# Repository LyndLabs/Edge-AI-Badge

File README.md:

# Edge AI Foundation Badge

The Edge AI Badge lets you plug-and-play with the latest vendor hardware at conference workshops and wirelessly connect with other attendees! Use the badge to explore the Edge AI curriculum, plug into sensors, and start building apps.

- 📄 [Read the docs →](https://lyndlabs.github.io/edge-ai-badge-docs)
- 💻 [Download or contribute to firmware](https://github.com/lyndlabs/edge-ai-badge-firmware).

## Hardware 
The badge is a modular PCB that allows you to customize your own face & backplates - the hardware platform is consistent at future conferences and makes it easy for attendees to design their own add-ons, or vendors that want to contribute hardware. 

It's built around the ESP32-S3, selected for its cryptographic core + secure boot, communication protocols (WiFi, BLE, ESP-NOW), infrared hardware, native USB, and ubiquitous support.

---

## Contents
- **assets**: logos, renders, global design assets
    - *find local assets under subfolders*
- **pcb**: KiCAD design files for `main`, `face`, `back`
- **fab**: production-ready pcb + laser files

## Versions & Notes
Versions bumped per batch release, revisions tracked for minor design changes per board - `main`, `face`, `back` tracked separately.

### v1 
- [x] Fixed USB + Power Path + XTAL issue 
- [ ] Buttons on resistor ladder
- [ ] Power button to MCU
- [ ] Standoff drill
- [ ] Interrupt to expansion
- [ ] Diode on USB 

### v0 - 26/06/08
- Main boards + backplate only - released in green HASL
- Wrong SMD standoff drilling size + CPL in production batch - used regular standoffs
- CPL + BOM discrepancy, released for visibility but pls do not order
- Known issue with USB charging
- Known issue w. Deep Sleep (.1uF caps on xtal)

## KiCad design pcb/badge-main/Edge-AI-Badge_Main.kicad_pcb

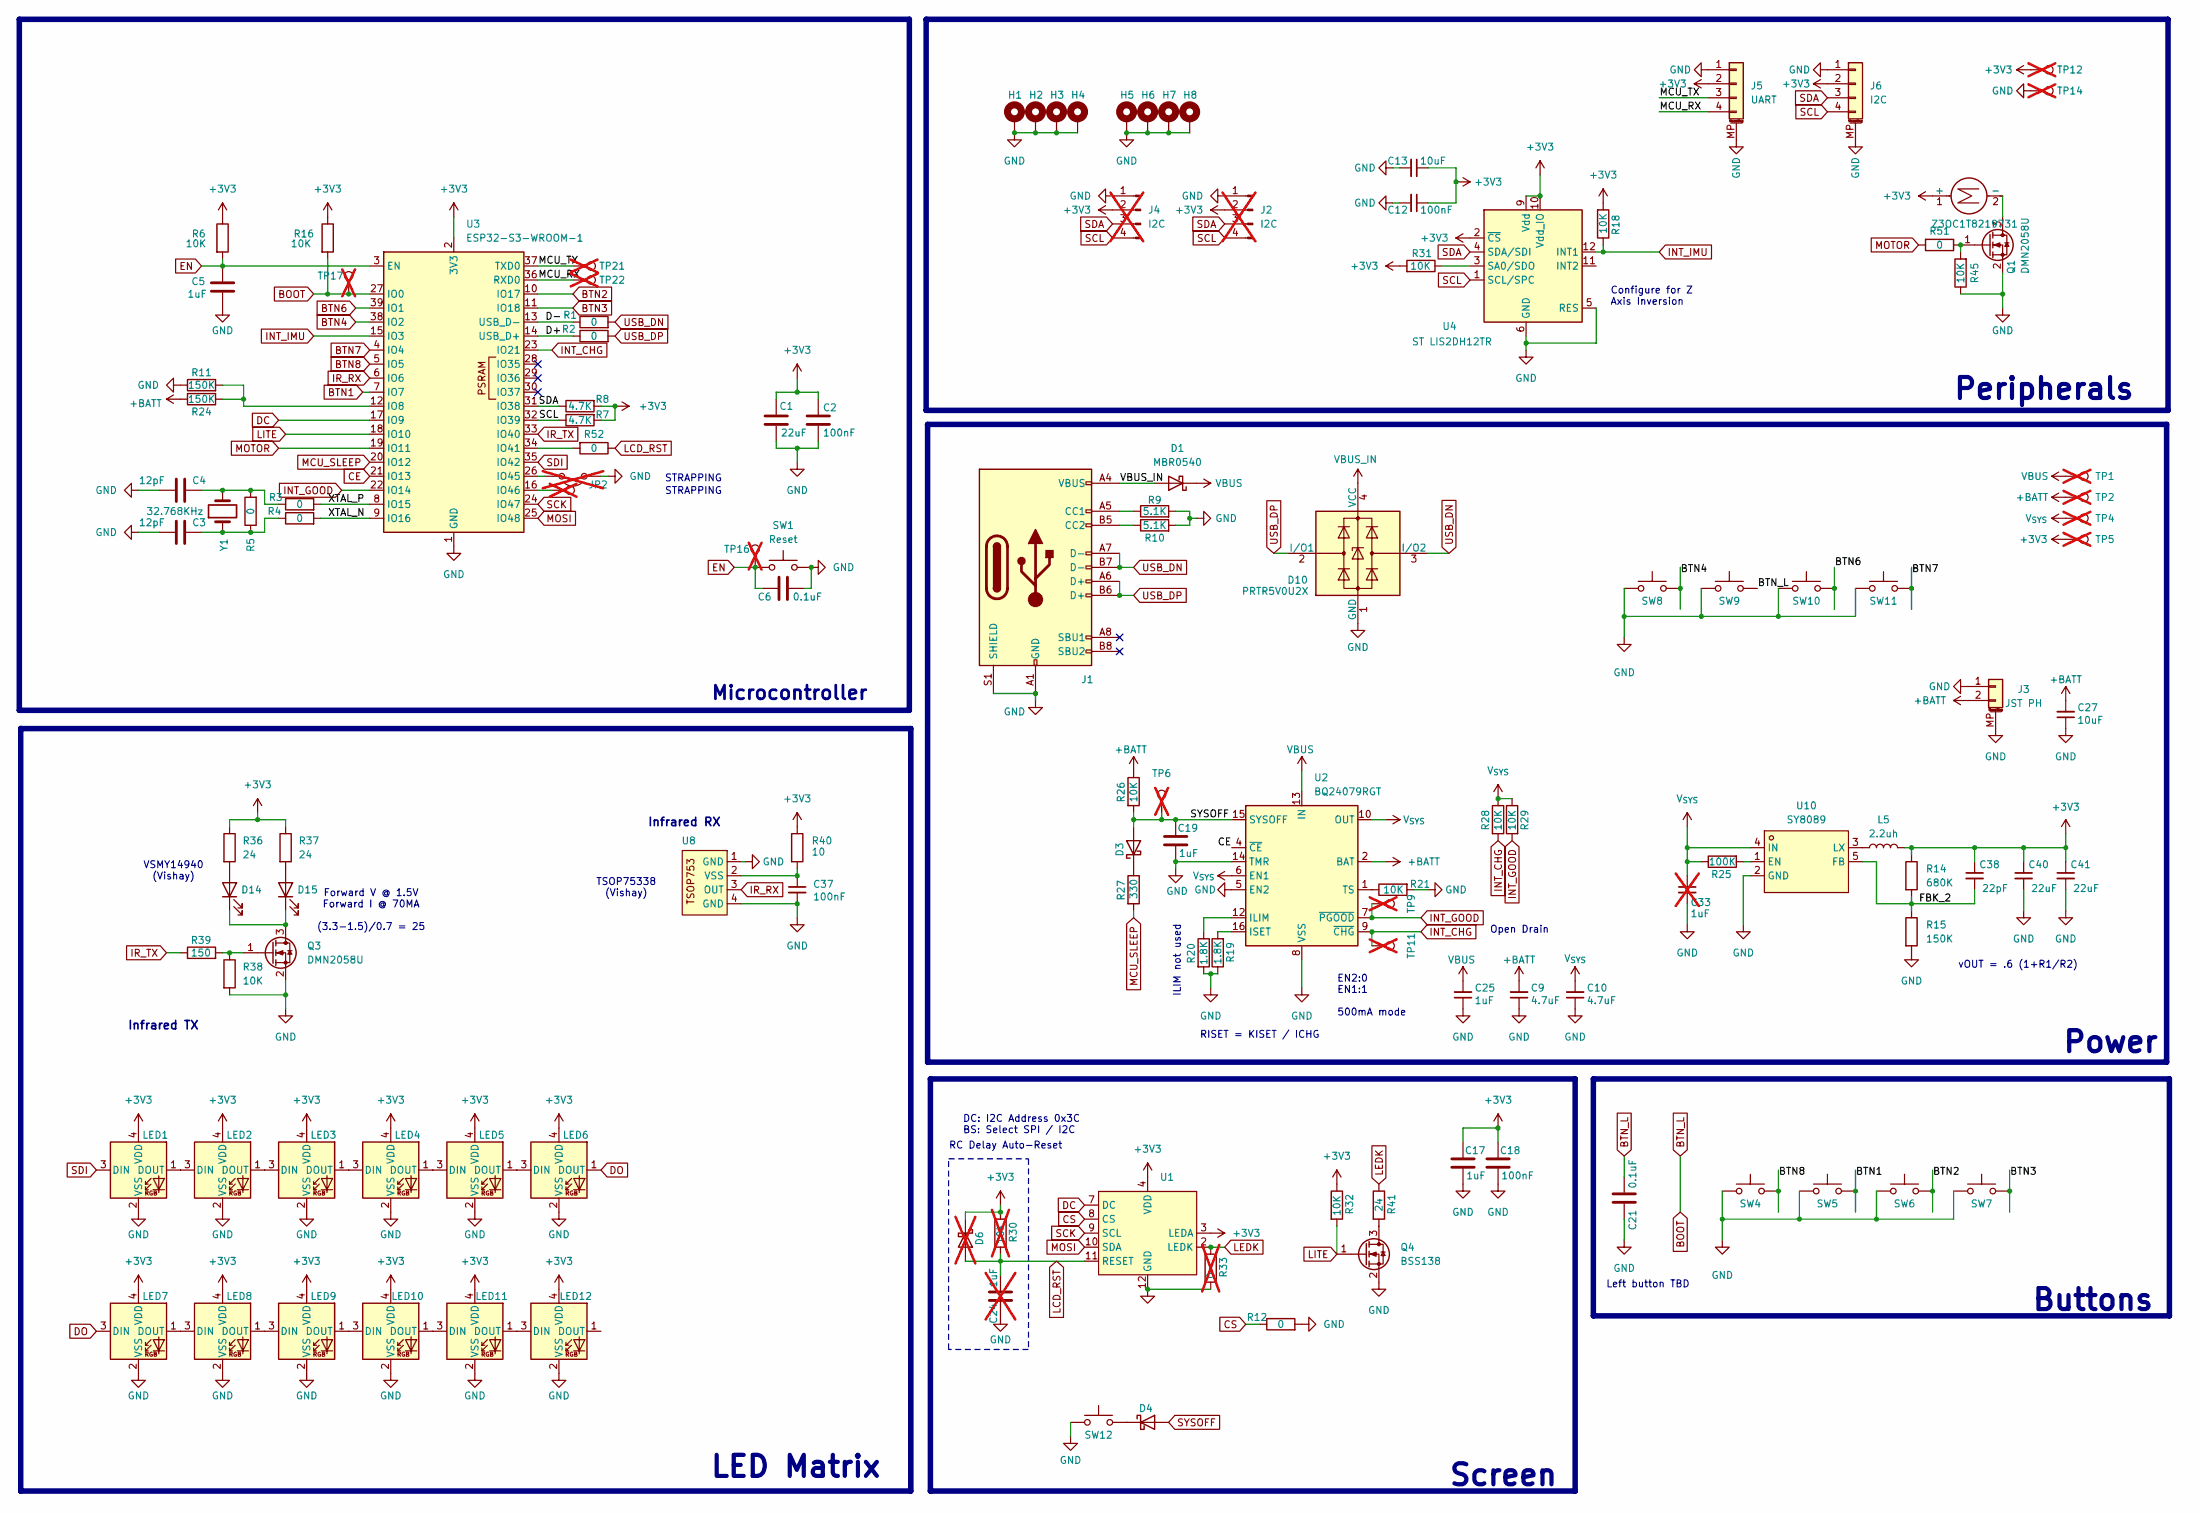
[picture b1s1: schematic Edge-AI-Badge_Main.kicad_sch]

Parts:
C1, C40, C41: 22uF; C_0402_1005Metric; LCSC C3845593
C2, C12, C18, C37: 100nF; C_0402_1005Metric; LCSC C1525
C3, C4: 12pF; C_0402_1005Metric; LCSC C1525
C5, C17, C19, C25: 1uF; C_0402_1005Metric; LCSC C14445
C6, C21: 0.1uF; C_0402_1005Metric; LCSC C1525
C9, C10: 4.7uF; C_0402_1005Metric; LCSC C315248
C13, C27: 10uF; C_0402_1005Metric; LCSC C315248
C24: 1uF; C_0402_1005Metric; LCSC C14445; not fitted
C33: 1uF; C_0402_1005Metric; LCSC C3845593; not fitted
C38: 22pF; C_0402_1005Metric; LCSC C76960
D1: MBR0540; D_SOD-123
D3, D4: D_Schottky; D_SOD-523; LCSC C917006
D6: D_Schottky; D_SOD-523; LCSC C917006; not fitted
D10: PRTR5V0U2X; SOT-143; LCSC C5180302
D14, D15: VSMY14940; vsmy14940; LCSC C511069
H1, H2, H3, H4, H5, H6, H7, H8: MountingHole_Pad
J1: USB C 2.0; USB_C_Receptacle_Palconn_UTC16-G; LCSC C2765186
J2, J4: I2C; PinSocket_1x04_P2.54mm_Vertical; not fitted
J3: JST PH; JST_PH_S2B-PH-SM4-TB_1x02-1MP_P2.00mm_Horizontal; LCSC C295747
J5: UART
J6: I2C
JP2: Jumper_2_Open; SolderJumper-2_P1.3mm_Open_RoundedPad1.0x1.5mm; not fitted
L5: 2.2uh; L_Coilcraft_LPS3010; LCSC C2926400
LED1, LED2, LED3, LED4, LED5, LED6, LED7, LED8, LED9, LED10, LED11, LED12: WS2812B-2020; LED_WS2812B-2020_PLCC4_2.0x2.0mm
M1: Z3OC1T8219731
Q1, Q3: DMN2058U; SOT-23; LCSC C461001
Q4: BSS138; SOT-23
R1, R2, R3, R4, R5, R12: 0; R_0201_0603Metric; LCSC C106228
R6, R16, R18, R21, R31, R32, R38, R45: 10K; R_0402_1005Metric; LCSC C60490
R7, R8: 4.7K; R_0402_1005Metric; LCSC C105871
R9, R10: 5.1K; R_0402_1005Metric; LCSC C25905
R11, R15, R24: 150K; R_0402_1005Metric; LCSC C93947
R14: 680K; R_0402_1005Metric; LCSC C163456
R19, R20: 1.8K; R_0402_1005Metric; LCSC C203083
R25: 100K; R_0402_1005Metric; LCSC C60491
R26, R28, R29: 10K; R_0402_1005Metric; LCSC C25767
R27: 330; R_0402_1005Metric; LCSC C112291
R30: 10K; R_0402_1005Metric; LCSC C60490; not fitted
R33: 0; R_0402_1005Metric; LCSC C60490; not fitted
R36, R37, R41: 24; R_0402_1005Metric; LCSC C270625
R39: 150; R_0402_1005Metric; LCSC C138054
R40: 10; R_0402_1005Metric; LCSC C138066
R51, R52: 0; R_0402_1005Metric; LCSC C106228
SW1: Reset; LCSC C231329
SW4, SW5, SW6, SW7, SW8, SW9, SW10, SW11, SW12: SW_Push; LCSC C25168849
TP1, TP2, TP4, TP5, TP6, TP8, TP9, TP11, TP12, TP14, TP16, TP17, TP21, TP22: TestPoint; TestPoint_Pad_D1.0mm; not fitted
U1: GC9A01
U2: BQ24079RGT; VQFN-16-1EP_3x3mm_P0.5mm_EP1.6x1.6mm; LCSC C2876751
U3: ESP32-S3-WROOM-1; LCSC C2913202
U4: ST LIS2DH12TR; LGA-12_2x2mm_P0.5mm; LCSC C110926
U8: TSOP75338; TSOP753; LCSC C499550
U10: SY8089; SOT-23-5; LCSC Part C79313
Y1: 32.768KHz; Crystal_SMD_3215-2Pin_3.2x1.5mm; LCSC C97606

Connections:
+3V3: C1.1, C2.1, C12.1, C13.1, C17.1, C18.1, C38.1, C40.1, C41.1, D6.1 (K), J2.2, J4.2, J5.2, J6.2, L5.2, LED1.4 (VDD), LED2.4 (VDD), LED3.4 (VDD), LED4.4 (VDD), LED5.4 (VDD), LED6.4 (VDD), LED7.4 (VDD), LED8.4 (VDD), LED9.4 (VDD), LED10.4 (VDD), LED11.4 (VDD), LED12.4 (VDD), M1.1 (+), R6.1, R7.2, R8.2, R14.1, R16.1, R18.2, R30.1, R31.2, R32.1, R36.1, R37.1, R40.1, TP5.1 (1_1), TP12.1 (1_1), U1.3 (LEDA), U1.4 (VDD), U3.2 (3V3), U4.2 (~CS), U4.9 (Vdd), U4.10 (Vdd_IO)
+BATT: C9.2, C27.2, J3.2, R24.1, R26.1, TP2.1 (1_1), U2.2 (BAT), U2.3 (BAT)
/D+: R2.1, U3.14 (USB_D+)
/D-: R1.1, U3.13 (USB_D-)
/FBK_2: C38.2, R14.2, R15.1, U10.5 (FB)
/MCU_RX: J5.4, TP22.1 (1_1), U3.36 (RXD0)
/MCU_TX: J5.3, TP21.1 (1_1), U3.37 (TXD0)
/XTAL_N: R4.2, U3.9 (IO16)
/XTAL_P: R3.2, U3.8 (IO15)
BOOT: C21.2, R16.2, SW9.2, TP17.1 (1_1), U3.27 (IO0)
BTN1: SW5.2, U3.7 (IO7)
BTN2: SW6.2, U3.10 (IO17)
BTN3: SW7.2, U3.11 (IO18)
BTN4: SW8.2, U3.38 (IO2)
BTN6: SW10.2, U3.39 (IO1)
BTN7: SW11.2, U3.4 (IO4)
BTN8: SW4.2, U3.5 (IO5)
CE: U2.4 (~CE), U3.21 (IO13)
CS: R12.1, U1.8 (CS)
DC: U1.7 (DC), U3.17 (IO9)
DO: LED6.1 (DOUT), LED7.3 (DIN)
EN: C5.1, C6.1, R6.2, SW1.2, TP16.1 (1_1), U3.3 (EN)
GND: C1.2, C2.2, C3.2, C4.2, C5.2, C6.2, C9.1, C10.1, C12.2, C13.2, C17.2, C18.2, C19.2, C21.1, C24.2, C25.1, C27.1, C33.2, C37.2, C40.2, C41.2, D10.1 (GND), H1.1 (1_1), H2.1 (1_1), H3.1 (1_1), H4.1 (1_1), H5.1 (1_1), H6.1 (1_1), H7.1 (1_1), H8.1 (1_1), J1.A1 (GND), J1.A12 (GND), J1.B1 (GND), J1.B12 (GND), J1.S1 (SHIELD), J2.1, J3.1, J3.MP (MountPin), J4.1, J5.1, J5.MP (MountPin), J6.1, J6.MP (MountPin), JP2.2 (B), LED1.2 (VSS), LED2.2 (VSS), LED3.2 (VSS), LED4.2 (VSS), LED5.2 (VSS), LED6.2 (VSS), LED7.2 (VSS), LED8.2 (VSS), LED9.2 (VSS), LED10.2 (VSS), LED11.2 (VSS), LED12.2 (VSS), Q1.2 (S), Q3.2 (S), Q4.2 (S), R9.2, R10.2, R11.1, R12.2, R15.2, R19.1, R20.2, R21.2, R33.2, R38.2, R45.1, SW1.1, SW4.1, SW5.1, SW6.1, SW7.1, SW8.1, SW9.1, SW10.1, SW11.1, SW12.1, TP14.1 (1_1), U1.1 (GND), U1.5 (GND), U1.6 (GND), U1.12 (GND), U2.5 (EN2), U2.8 (VSS), U2.14 (TMR), U2.17 (VSS), U3.1 (GND), U3.40 (GND), U3.41 (GND), U4.5 (RES), U4.6 (GND), U4.7 (GND), U4.8 (GND), U8.1 (GND), U8.4 (GND), U10.2 (GND)
INT_CHG: R28.2, TP11.1 (1_1), U2.9 (~CHG), U3.23 (IO21)
INT_GOOD: R29.2, TP9.1 (1_1), U2.7 (~PGOOD), U3.22 (IO14)
INT_IMU: R18.1, U3.15 (IO3), U4.12 (INT1)
IR_RX: U3.6 (IO6), U8.3 (OUT)
IR_TX: R39.1, U3.33 (IO40)
LCD_RST: C24.1, D6.2 (A), R30.2, R52.1, U1.11 (RESET)
LEDK: R33.1, R41.1, U1.2 (LEDK)
LITE: Q4.1 (G), R32.2, U3.18 (IO10)
MCU_SLEEP: R27.2, U3.20 (IO12)
MOSI: U1.10 (SDA), U3.25 (IO48)
MOTOR: R51.2, U3.19 (IO11)
unnamed: C3.1, R4.1, R5.1, Y1.1
unnamed: C4.1, R3.1, R5.2, Y1.2
unnamed: D3.1 (K), R27.1
unnamed: D4.1 (K), SW12.2
unnamed: D14.2 (A), R36.2
unnamed: D14.1 (K), D15.1 (K), Q3.3 (D)
unnamed: D15.2 (A), R37.2
unnamed: J1.A5 (CC1), R9.1
unnamed: J1.B5 (CC2), R10.1
unnamed: JP2.1 (A), U3.26 (IO45)
unnamed: LED1.1 (DOUT), LED2.3 (DIN)
unnamed: LED2.1 (DOUT), LED3.3 (DIN)
unnamed: LED3.1 (DOUT), LED4.3 (DIN)
unnamed: LED4.1 (DOUT), LED5.3 (DIN)
unnamed: LED5.1 (DOUT), LED6.3 (DIN)
unnamed: LED7.1 (DOUT), LED8.3 (DIN)
unnamed: LED8.1 (DOUT), LED9.3 (DIN)
unnamed: LED9.1 (DOUT), LED10.3 (DIN)
unnamed: LED10.1 (DOUT), LED11.3 (DIN)
unnamed: LED11.1 (DOUT), LED12.3 (DIN)
unnamed: M1.2 (-), Q1.3 (D)
unnamed: Q1.1 (G), R45.2, R51.1
unnamed: Q3.1 (G), R38.1, R39.2
unnamed: Q4.3 (D), R41.2
unnamed: R20.1, U2.12 (ILIM)
unnamed: R19.2, U2.16 (ISET)
unnamed: R21.1, U2.1 (TS)
unnamed: R11.2, R24.2, U3.12 (IO8)
unnamed: R52.2, U3.34 (IO41)
unnamed: TP8.1 (1_1), U3.16 (IO46)
unnamed: R31.1, U4.3 (SA0/SDO)
unnamed: C37.1, R40.2, U8.2 (VSS)
unnamed: R25.2, U10.1 (EN)
unnamed: L5.1, U10.3 (LX)
SCK: U1.9 (SCL), U3.24 (IO47)
SCL: J2.4, J4.4, J6.4, R7.1, U3.32 (IO39), U4.1 (SCL/SPC)
SDA: J2.3, J4.3, J6.3, R8.1, U3.31 (IO38), U4.4 (SDA/SDI)
SDI: LED1.3 (DIN), U3.35 (IO42)
SYSOFF: C19.1, D3.2 (A), D4.2 (A), R26.2, TP6.1 (1_1), U2.15 (SYSOFF)
USB_DN: D10.3 (I/O2), J1.A7 (D-), J1.B7 (D-), R1.2
USB_DP: D10.2 (I/O1), J1.A6 (D+), J1.B6 (D+), R2.2
VBUS: C25.2, D1.1 (K), TP1.1 (1_1), U2.13 (IN)
VBUS_IN: D1.2 (A), D10.4 (VCC), J1.A4 (VBUS), J1.A9 (VBUS), J1.B4 (VBUS), J1.B9 (VBUS)
V_{SYS}: C10.2, C33.1, R25.1, R28.1, R29.1, TP4.1 (1_1), U2.6 (EN1), U2.10 (OUT), U2.11 (OUT), U10.4 (IN)

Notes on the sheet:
Configure for Z Axis Inversion
STRAPPING
VSMY14940 (Vishay)
Buttons
vOUT = .6 (1+R1/R2)
Forward V @ 1.5V Forward I @ 70MA (3.3-1.5)/0.7 = 25
Infrared RX
Microcontroller
RC Delay Auto-Reset
Peripherals
TSOP75338 (Vishay)
LED Matrix
Infrared TX
RISET = KISET / ICHG
DC: I2C Address 0x3C BS: Select SPI / I2C
Left button TBD
Screen
ILIM not used
Open Drain
Power
EN2:0 EN1:1 500mA mode

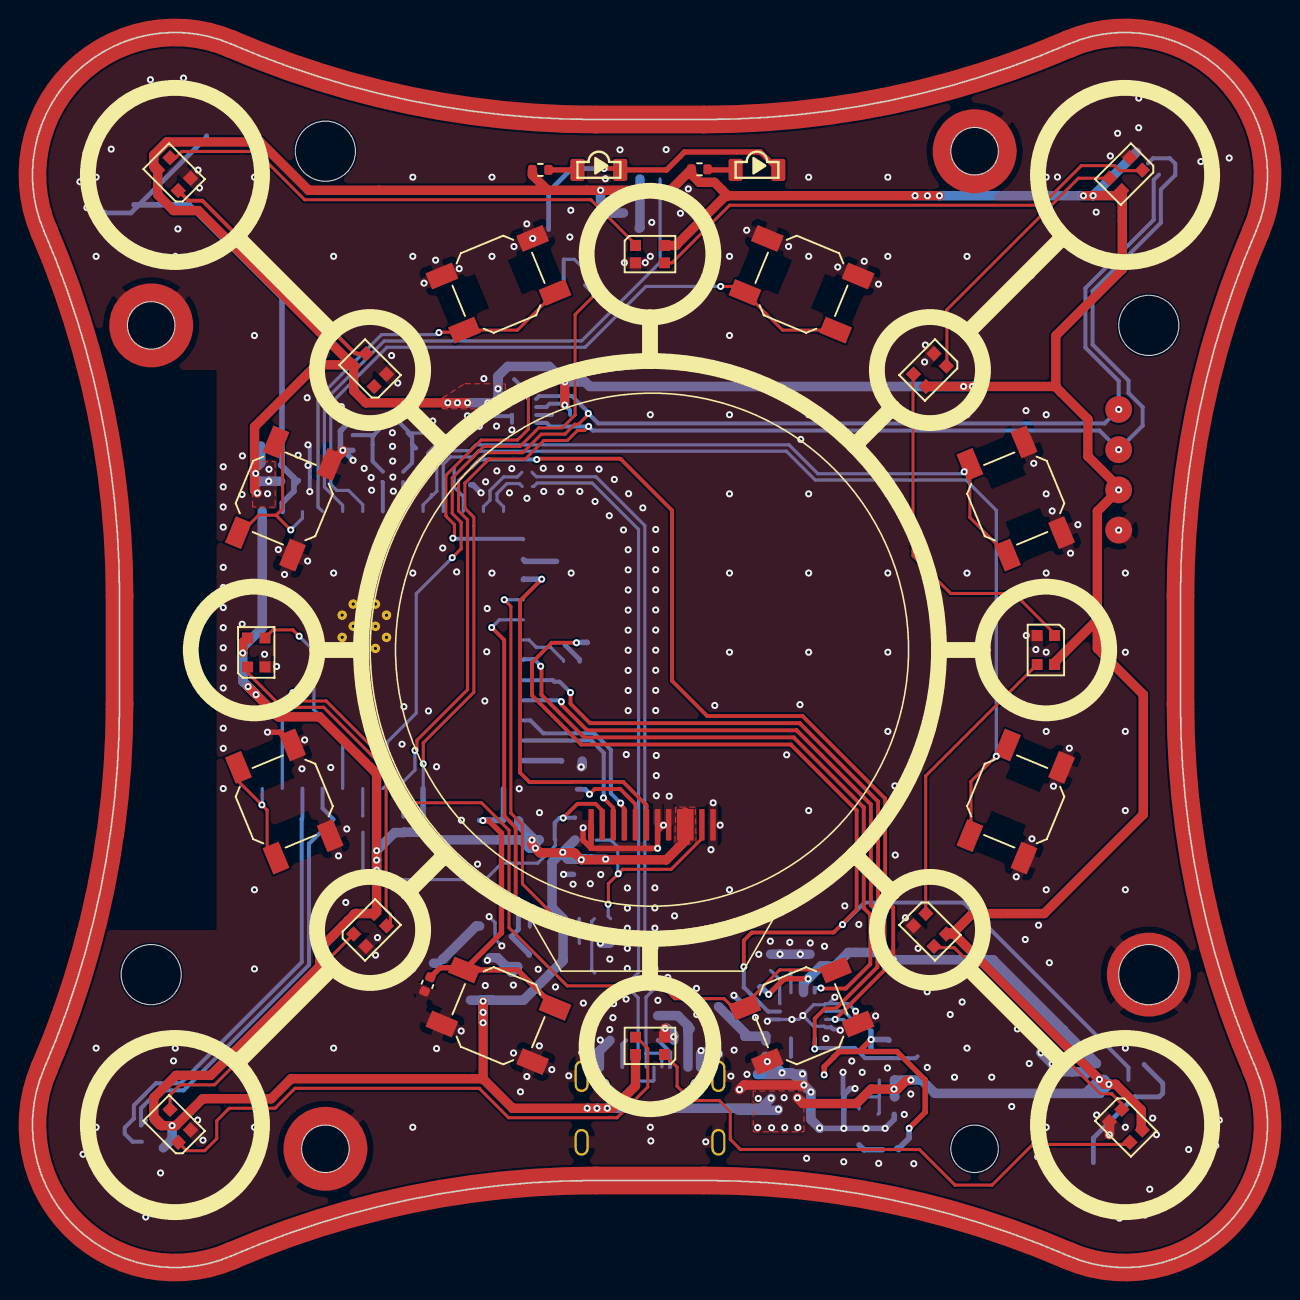
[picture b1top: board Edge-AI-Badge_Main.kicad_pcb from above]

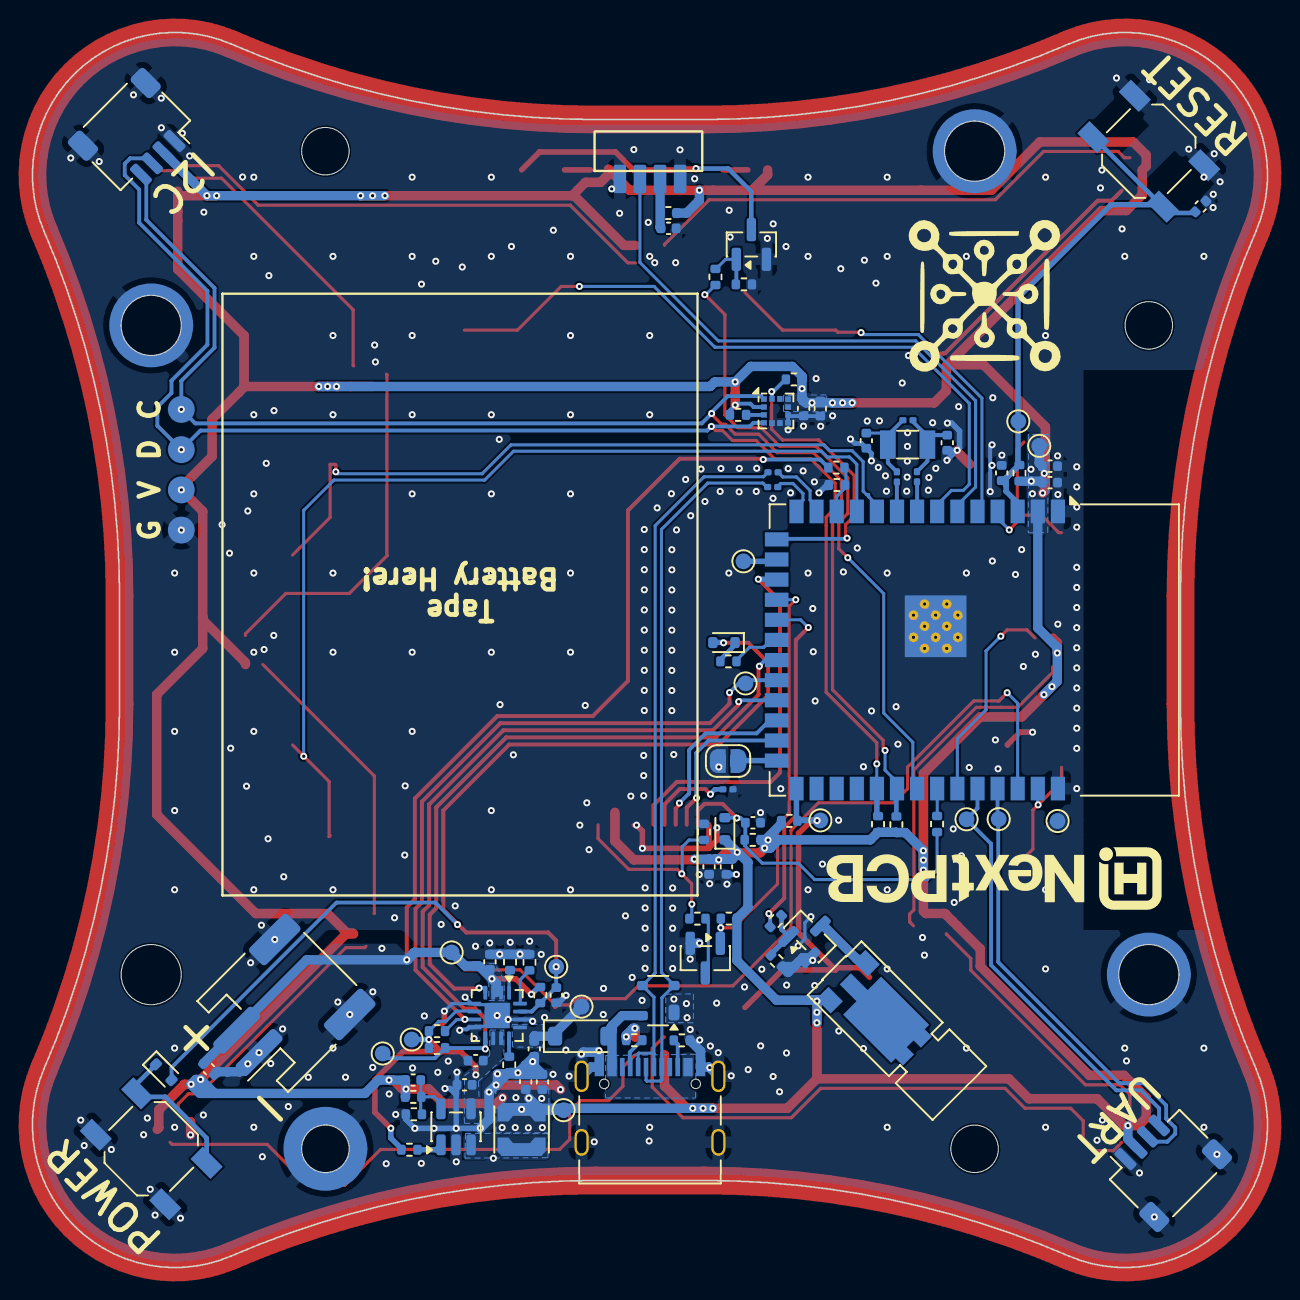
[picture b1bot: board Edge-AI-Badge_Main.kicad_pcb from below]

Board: 2 copper layers, 78.0 x 78.0 mm, 130 parts (99 on the bottom side), 78 nets.

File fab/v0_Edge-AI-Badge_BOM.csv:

Reference,Value,DNP,Footprint,Datasheet,LCSC
"C1,C40,C41",22uF,,Capacitor_SMD:C_0402_1005Metric,,C3845593
"C2,C12,C18,C37",100nF,,Capacitor_SMD:C_0402_1005Metric,,C1525
"C3,C4,C6,C21",0.1uF,,Capacitor_SMD:C_0402_1005Metric,,C1525
"C5,C17,C19,C24,C25,C33",1uF,,Capacitor_SMD:C_0402_1005Metric,,"C14445,C3845593"
"C9,C10",4.7uF,,Capacitor_SMD:C_0402_1005Metric,,C315248
"C13,C27",10uF,,Capacitor_SMD:C_0402_1005Metric,,C315248
C38,22pF,,Capacitor_SMD:C_0402_1005Metric,,C76960
"D1,D3,D4,D6",D_Schottky,,Diode_SMD:D_SOD-523,,C917006
D10,PRTR5V0U2X,,Package_TO_SOT_SMD:SOT-143,https://assets.nexperia.com/documents/data-sheet/PRTR5V0U2X.pdf,C5180302
"D14,D15",VSMY14940,,Temporal:vsmy14940,,C511069
"H1,H2,H3,H4",M2 x 1.5mm,,,,C5301775
"H5,H6,H7,H8",M2x6mm,,,,C5301797
J1,USB C 2.0,,Connector_USB:USB_C_Receptacle_Palconn_UTC16-G,https://www.usb.org/sites/default/files/documents/usb_type-c.zip,C2765186
J3,JST PH,,Connector_JST:JST_PH_S2B-PH-SM4-TB_1x02-1MP_P2.00mm_Horizontal,,C295747
"J5,J6",SM04B,,,,
L5,2.2uh,,Inductor_SMD:L_Coilcraft_LPS3010,https://www.lcsc.com/datasheet/lcsc_datasheet_2410121211_YJY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,C2926400
"LED1,LED2,LED3,LED4,LED5,LED6,LED7,LED8,LED9,LED10,LED11,LED12",APA102-2020,,LED_SMD:LED-APA102-2020,http://www.led-color.com/upload/201604/APA102-2020%20SMD%20LED.pdf,
M1,Z3OC1T8219731,,,,
"Q1,Q3",DMN2058U,,Package_TO_SOT_SMD:SOT-23,http://www.diodes.com/assets/Datasheets/DMN2058U.pdf,C461001
Q2,MMBT3904,,Package_TO_SOT_SMD:SOT-23,https://www.onsemi.com/pdf/datasheet/pzt3904-d.pdf,C916374
Q4,BSS138,,Package_TO_SOT_SMD:SOT-23,https://www.onsemi.com/pub/Collateral/BSS138-D.PDF,
"R1,R2,R3,R4,R5,R12",0,,Resistor_SMD:R_0201_0603Metric,,C106228
"R6,R16,R18,R21,R26,R28,R29,R30,R31,R32,R38,R45",10K,,Resistor_SMD:R_0402_1005Metric,,"C25767,C60490"
"R7,R8",4.7K,,Resistor_SMD:R_0402_1005Metric,,C105871
"R9,R10",5.1K,,Resistor_SMD:R_0402_1005Metric,,C25905
"R11,R15,R24",150K,,Resistor_SMD:R_0402_1005Metric,,C93947
R14,680K,,Resistor_SMD:R_0402_1005Metric,,C163456
"R19,R20",1.8K,,Resistor_SMD:R_0402_1005Metric,,C203083
R22,47K,,Resistor_SMD:R_0402_1005Metric,,C163456
"R23,R25",100K,,Resistor_SMD:R_0402_1005Metric,,C60491
R27,330,,Resistor_SMD:R_0402_1005Metric,,C112291
"R36,R37,R41",24,,Resistor_SMD:R_0402_1005Metric,,C270625
R39,150,,Resistor_SMD:R_0402_1005Metric,,C138054
R40,10,,Resistor_SMD:R_0402_1005Metric,,C138066
SW1,Reset,,,,C2762971
"SW1, SW4,SW5,SW6,SW7,SW8,SW9,SW10,SW11,SW12",SW_Push,,,,C2762971
U2,BQ24079RGT,,Package_DFN_QFN:VQFN-16-1EP_3x3mm_P0.5mm_EP1.6x1.6mm,http://www.ti.com/lit/ds/symlink/bq24079.pdf,C2876751
U3,ESP32-S3-WROOM-1,,RF_Module:ESP32-S3-WROOM-1,https://www.espressif.com/sites/default/files/documentation/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,C2913202
U4,ST LIS2DH12TR,,Package_LGA:LGA-12_2x2mm_P0.5mm,https://www.st.com/resource/en/datasheet/lis2DE12.pdf,C110926
U8,TSOP75338,,LyndLabs-Module:TSOP753,,C499550
U10,SY8089,,Package_TO_SOT_SMD:SOT-23-5,https://lcsc.com/product-detail/DC-DC-Converters_Silergy_SY8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,C79313
Y1,32.768KHz,,Crystal:Crystal_SMD_3215-2Pin_3.2x1.5mm,,C97606

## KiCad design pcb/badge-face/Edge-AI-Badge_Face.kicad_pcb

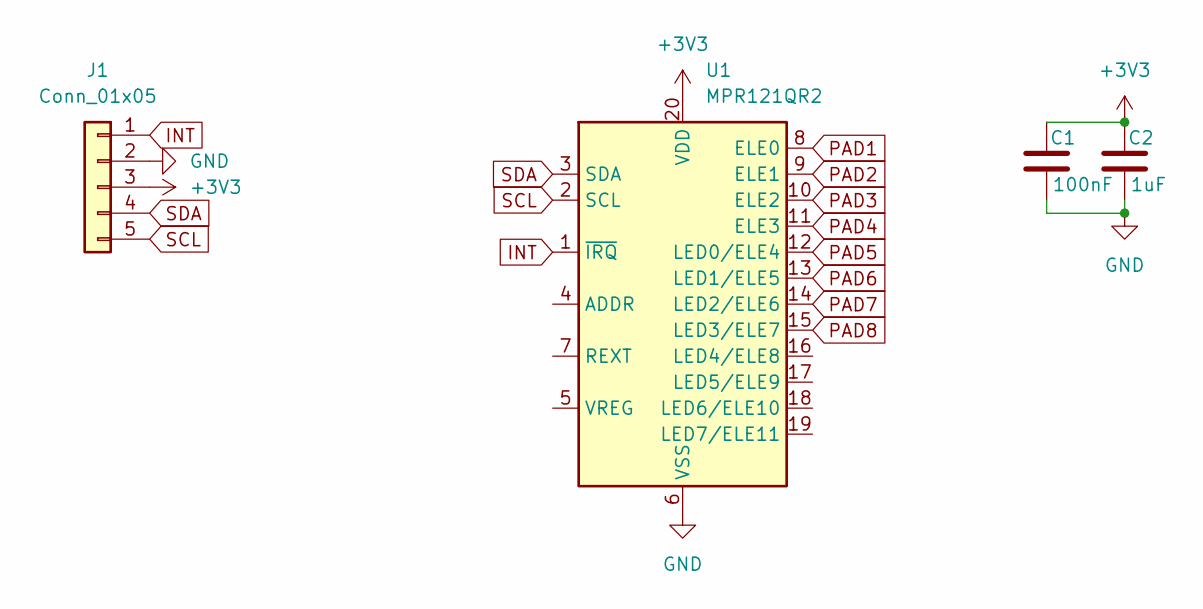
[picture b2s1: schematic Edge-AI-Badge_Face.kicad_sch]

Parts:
C1: 100nF; C_0402_1005Metric
C2: 1uF; C_0402_1005Metric
J1: Conn_01x05; PinSocket_1x05_P2.54mm_Vertical
U1: MPR121QR2; UQFN-20_3x3mm_P0.4mm

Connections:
+3V3: C1.1, C2.1, J1.3, U1.20 (VDD)
GND: C1.2, C2.2, J1.2, U1.6 (VSS)
INT: J1.1, U1.1 (~IRQ)
PAD1: U1.8 (ELE0)
PAD2: U1.9 (ELE1)
PAD3: U1.10 (ELE2)
PAD4: U1.11 (ELE3)
PAD5: U1.12 (LED0/ELE4)
PAD6: U1.13 (LED1/ELE5)
PAD7: U1.14 (LED2/ELE6)
PAD8: U1.15 (LED3/ELE7)
SCL: J1.5, U1.2 (SCL)
SDA: J1.4, U1.3 (SDA)

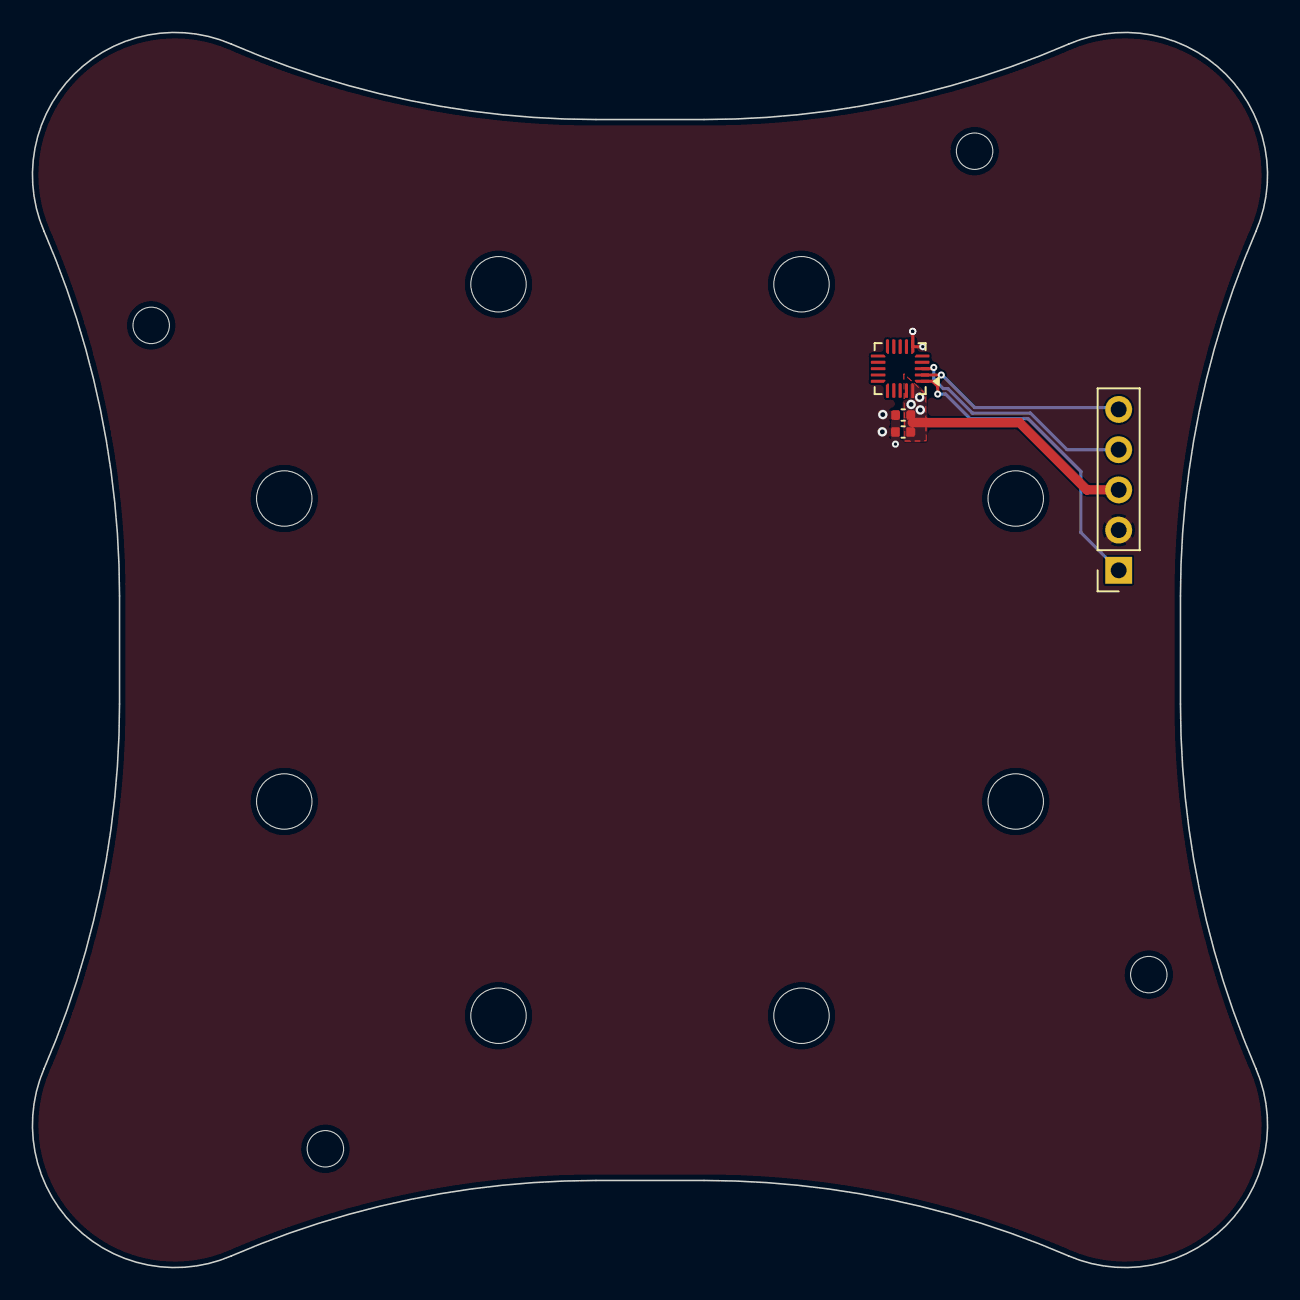
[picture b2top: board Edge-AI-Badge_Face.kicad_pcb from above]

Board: 2 copper layers, 78.0 x 78.0 mm, 4 parts (0 on the bottom side), 5 nets.

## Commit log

2026-06-17 push initial v0 design files
2026-06-17 organize some stuff
2026-06-17 update docs i guess
2026-06-17 gitignore
2026-06-17 some sch + pcb changes ...
